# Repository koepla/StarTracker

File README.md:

# StarTracker

This repository is part of the diploma thesis of `Ilja Roman Köhler` and `Elias Engelbert Plank`. In short, the goal is to provide a software and hardware solution for the following question: Which technologies and algorithms are necessary to automatically track a range of different celestial bodies with an off the shelf camera?

---

## Contributors

[`Ilja Roman Köhler`](https://github.com/KoehIl180151 "Hardware part")

Responsible for the hardware, which involves designing and putting together a circuit that uses the almighty `ATMega-328p` chip as well as `TMC2209 drivers`, design and construction of the 3D-printed parts of the tracking mount, and firmware development for the circuit.

[`Elias Engelbert Plank`](https://github.com/PlanEl180223 "Software part")

Responsible for most of the software, which involves the ephemeris engine and the actual client application.

---

## How does StarTracker work?

To achieve the above goal, a construction made with the help of FDM printing, a circuit board, and a specially developed software are used. Specifically, an off the shelf camera mounted on the construction can be moved to any point in the sky by using stepper motors. By calculating the position of any celestial body in the client application, one can point the camera at basically anything that has spherical coordinates.

### Construction

The FDM parts were designed in a way so that they can be easily procued with any 3D printer (even entry-level devices) and still have the necessary stability. We recommend using PETG over PLA filament due to its superior material properties. The entire 3D design process is done in `Autodesk Fusion 360`, since Autodesk offers free licences for students, as well as a tool for designing circuit boards (`Autodesk Eagle`).

### Electronics and circuit

The camera is steered by `Nema 17 stepper motors`, which offer the perfect balance of power and size. The motors are driven by `TMC-2209 drivers` due to their reliability and robustness. The heart of the circuit is a `ATMega-328p` microcontroller, currently in the form of an Arduino Nano. However, there are plans to replace the Arduino Nano with just the ATMega chip itself.

### Client application

The client application, which is developed as a graphical desktop application entirely in C++ and GLSL, has a list of celestial bodies whose position can be computed. This list can be extended by the user. The position of each celestial body in the sky is determined in real time using our own ephemeris engine. When the user selects a target object, the position data is transmitted via a two-way protocol to the microcontroller on the circuit, whereupon the microcontroller sets the stepper motors to the correct position.

---

## Building

First of all, you must have git and CMake installed. As we use presets for our CMake configuration, you need a relatively recent version that supports presets. It is extremely important, that the repository is clonsed recursively, due to the use of submodules.

### Windows

On Windows, it is recommended to use Visual Studio 2022 together with the CMake extension. CMake will grab the dependencies upon configure, therefore no libraries have to be manually installed. You can then open the src/libtracker folder with Visual Studio that contains the CMakeLists.txt file. After CMake will finish with the configuration, you can choose a preset and build the application.

### Linux

On Linux, it is recommended to use JetBrains CLion, as it integrates with CMake. If you already have `curl` and `libcurl4-openssl-dev` installed, the CMake configuration will use those. Otherwise, curl will be automatically fetched, therefore no install is required. You can then open the src/libtracker folder with CLion. After CMake will finish with the configuration, you can choose a preset and build the application.

Here's a folder structure to feel secure and find your way around:

```
[root repo folder]
  |
  + [doc] // containing detailed project documentation
  |   |
  |   + [progress_reports] // containing status reports
  |                        // additionally github projects is used for documentation 
  |
  + [hwr] // containg schematics of the hardware parts
  |
  + [src] // containing the actual source code
      |
      + [tracker] // containing the code of the client application
      |   |
      |   + [libengine] // holds the source code of the ephemeris engine, builds to static library
      |   |
      |   + [libtracker] // the actual client application, links with libengine
      |
      + [firmware] // containing the firmware for the circuit
```

---

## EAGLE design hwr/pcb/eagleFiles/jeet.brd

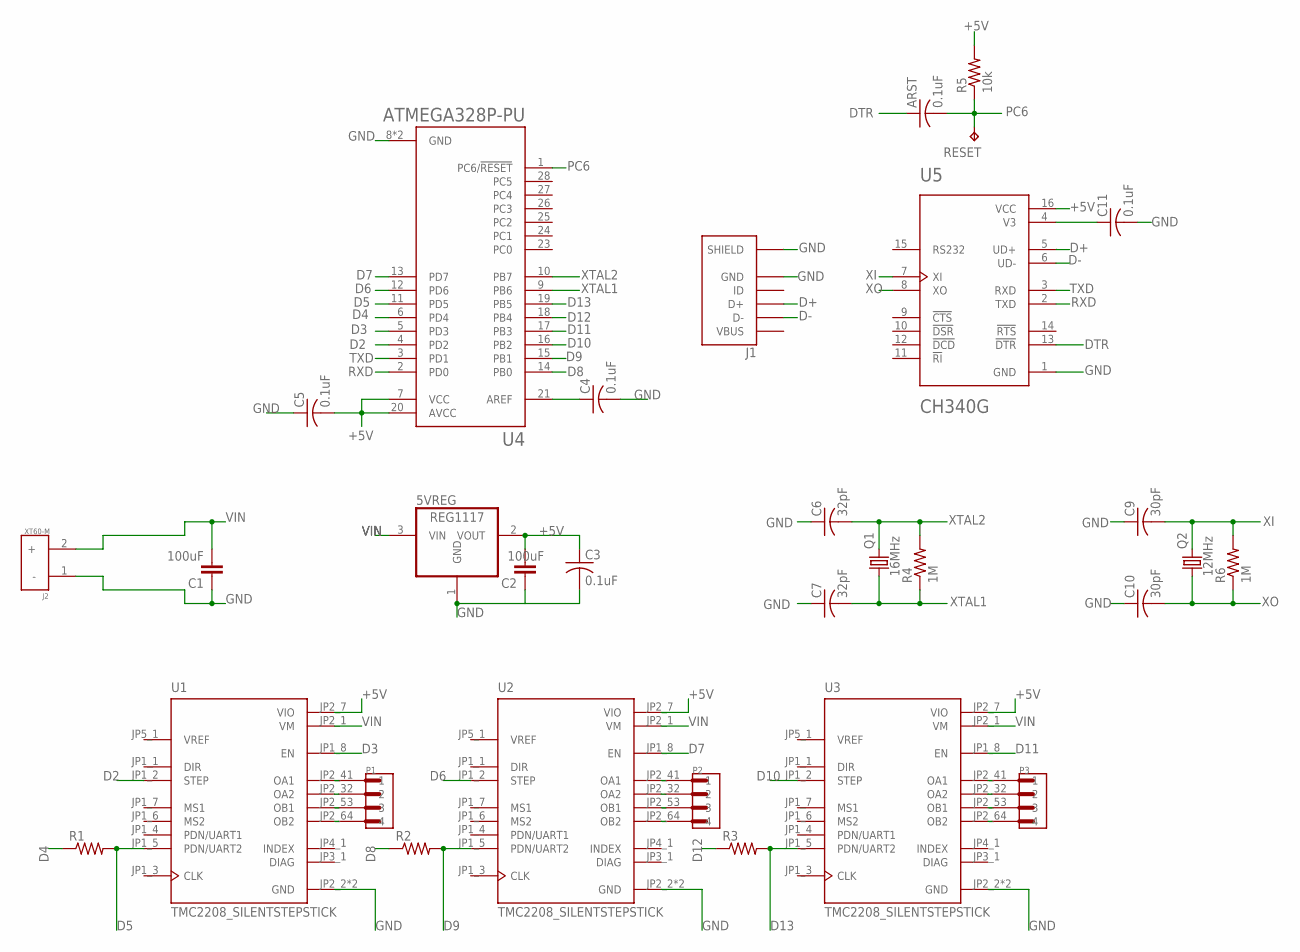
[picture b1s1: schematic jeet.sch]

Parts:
5VREG: REG1117; SOT223
ARST: 0.1uF; C0805
C1, C2: 100uF; C2.5-3
C3, C4, C5, C11: 0.1uF; C0805
C6, C7: 32pF; C0805
C9, C10: 30pF; C0805
J1: USB2066-05-RBHM-XX-STB-00-00-A_REVD; GCT_USB2066-05-RBHM-XX-STB-00-00-A_REVD
J2: XT60-M; AMASS_XT60-M
P1, P2, P3: S4B-XH-A(LF)(SN); JST_S4B-XH-A(LF)(SN)
Q1: 16MHz; HC49/S
Q2: 12MHz; HC49/S
R1, R2, R3: R-US_R0805; R0805
R4, R6: 1M; R0805
R5: 10k; R0805
RESET: TPB1,27; B1,27
U1, U2, U3: TMC2208_SILENTSTEPSTICK; MODULE_TMC2208_SILENTSTEPSTICK
U4: ATMEGA328P-PU; DIP794W46P254L2967H457Q28B
U5: CH340G; SOIC127P600X180-16N

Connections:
+5V: 5VREG.2 (VOUT), C2.2, C3.1, C5.2, R5.2, U1.JP2_7 (VIO), U2.JP2_7 (VIO), U3.JP2_7 (VIO), U4.7 (VCC), U4.20 (AVCC), U5.16 (VCC)
D2: U1.JP1_2 (STEP), U4.4 (PD2)
D3: U1.JP1_8 (EN), U4.5 (PD3)
D4: R1.1, U4.6 (PD4)
D5: R1.2, U1.JP1_5 (PDN/UART2), U4.11 (PD5)
D6: U2.JP1_2 (STEP), U4.12 (PD6)
D7: U2.JP1_8 (EN), U4.13 (PD7)
D8: R2.1, U4.14 (PB0)
D9: R2.2, U2.JP1_5 (PDN/UART2), U4.15 (PB1)
D10: U3.JP1_2 (STEP), U4.16 (PB2)
D11: U3.JP1_8 (EN), U4.17 (PB3)
D12: R3.1, U4.18 (PB4)
D13: R3.2, U3.JP1_5 (PDN/UART2), U4.19 (PB5)
D+: J1.3 (D+), U5.5 (UD+)
D-: J1.2 (D-), U5.6 (UD-)
DTR: ARST.1, U5.13 (!DTR)
GND: 5VREG.1 (GND), C1.1, C2.1, C3.2, C4.2, C5.1, C6.1, C7.1, C9.1, C10.1, C11.2, J1.5 (GND), J1.6 (SHIELD), J1.7 (SHIELD), J1.8 (SHIELD), J1.9 (SHIELD), J2.1 (-), U1.JP2_2 (GND), U1.JP2_8 (GND), U2.JP2_2 (GND), U2.JP2_8 (GND), U3.JP2_2 (GND), U3.JP2_8 (GND), U4.8 (GND), U4.22 (GND), U5.1 (GND)
unnamed: P1.1, U1.JP2_4 (OA1)
unnamed: P1.2, U1.JP2_3 (OA2)
unnamed: P1.3, U1.JP2_5 (OB1)
unnamed: P1.4, U1.JP2_6 (OB2)
unnamed: P2.1, U2.JP2_4 (OA1)
unnamed: P2.2, U2.JP2_3 (OA2)
unnamed: P2.3, U2.JP2_5 (OB1)
unnamed: P2.4, U2.JP2_6 (OB2)
unnamed: P3.1, U3.JP2_4 (OA1)
unnamed: P3.2, U3.JP2_3 (OA2)
unnamed: P3.3, U3.JP2_5 (OB1)
unnamed: P3.4, U3.JP2_6 (OB2)
unnamed: C4.1, U4.21 (AREF)
unnamed: C11.1, U5.4 (V3)
PC6: ARST.2, R5.1, RESET.TP, U4.1 (PC6/!RESET)
RXD: U4.2 (PD0), U5.2 (TXD)
TXD: U4.3 (PD1), U5.3 (RXD)
VBUS: J1.1 (VBUS)
VIN: 5VREG.3 (VIN), C1.2, J2.2 (+), U1.JP2_1 (VM), U2.JP2_1 (VM), U3.JP2_1 (VM)
XI: C9.2, Q2.2, R6.2, U5.7 (XI)
XO: C10.2, Q2.1, R6.1, U5.8 (XO)
XTAL1: C7.2, Q1.1, R4.1, U4.9 (PB6)
XTAL2: C6.2, Q1.2, R4.2, U4.10 (PB7)

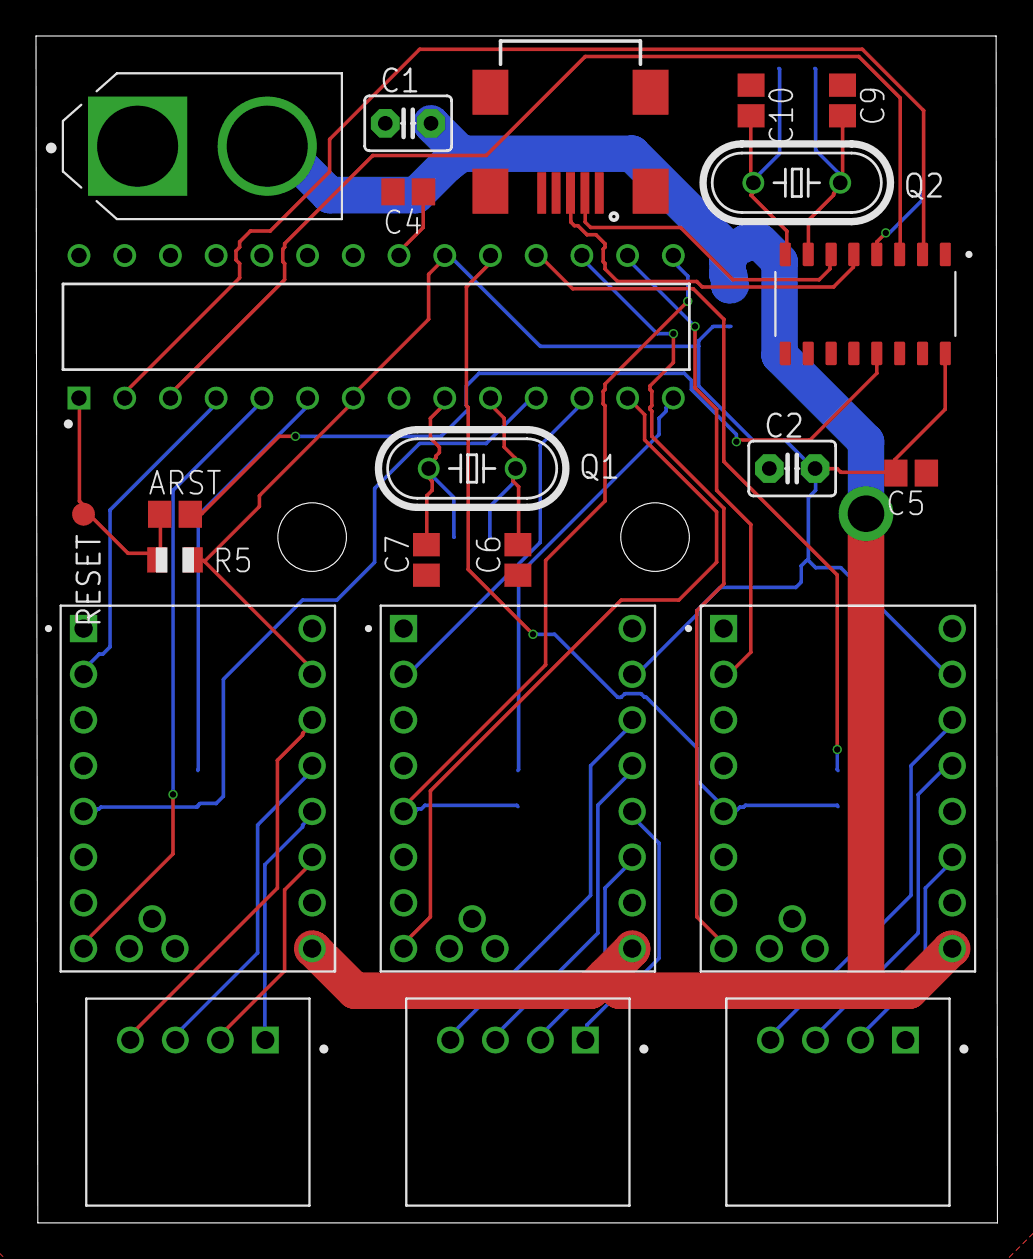
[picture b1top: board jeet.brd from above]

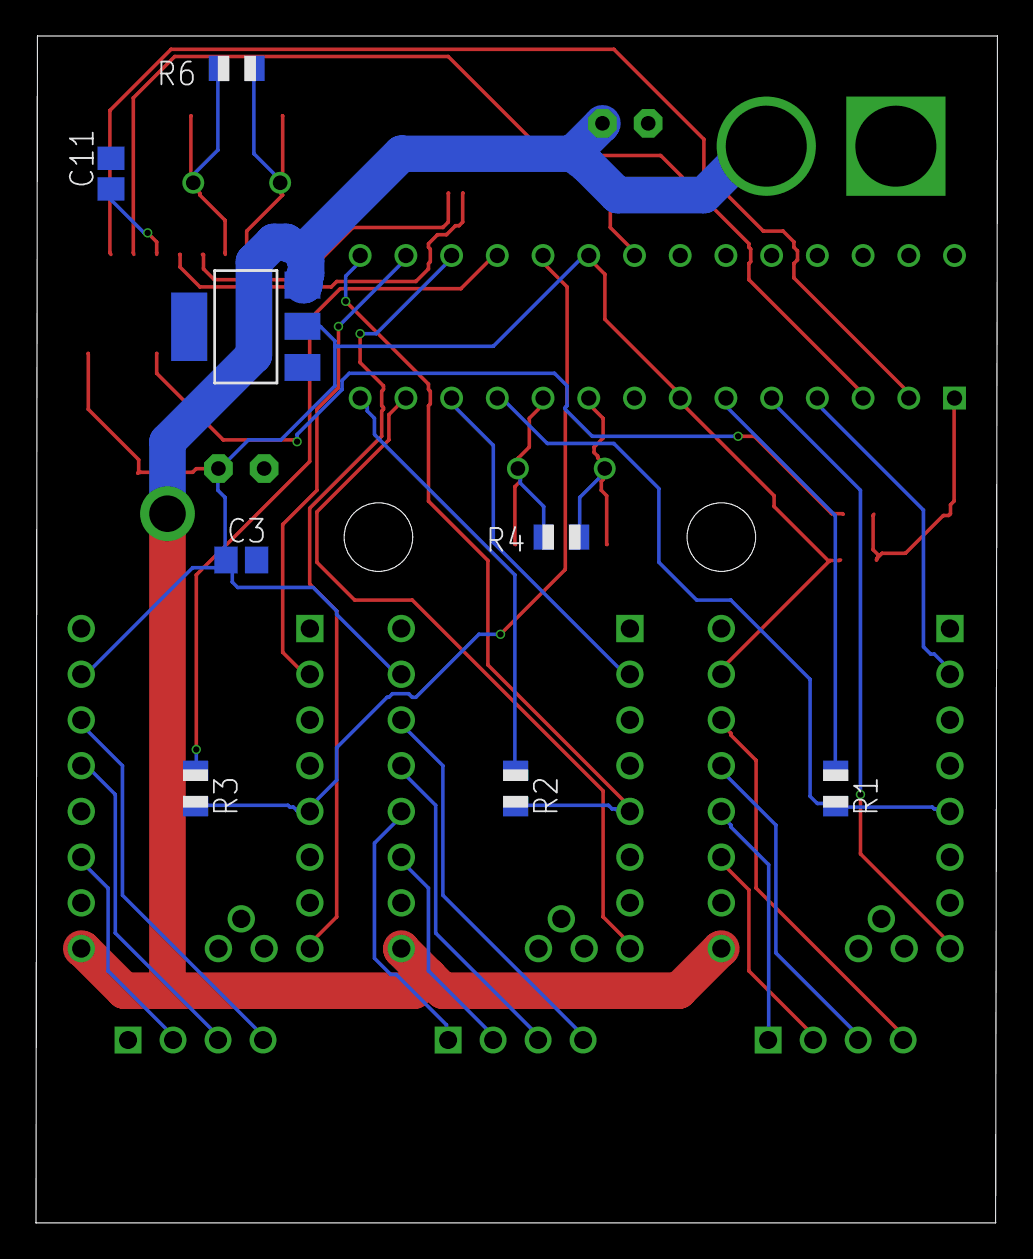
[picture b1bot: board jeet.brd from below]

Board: 4 copper layers, 53.4 x 65.9 mm, 31 parts (8 on the bottom side), 39 nets.

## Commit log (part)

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2021-11-04 accuracy
2021-11-04 code for testing
2021-11-04 can be const
2021-11-04 refactor
2021-11-04 more debug info
2021-11-04 temporary fix for coordinate transform
    the computed gmst was actually the local mean sidereal time, due to the fact that we passed the local time. If we want to still name the function Gmst, then we would only be allowed to pass the relat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
2021-11-04 added temporary compiler warning for potential unwanted behaviour in lmst function
2021-11-06 Added ability to adjust the tracker origin in softWare
2021-11-06 updated cli and added option for manual body
2021-11-13 added code for adding and subtracting parts of datetime
2021-11-13 fixed the issue with the computation of the local mean sidereal time
2021-11-13 testcases for the new datetime functions and sidereal time
2021-11-13 added serial to utils namespace
2021-11-14 removed testcases for datetime
2021-11-14 previous celestialbody is now solarsystem body
    added capability to add fixed bodies, previous celestialbody is now solarsystembody, LoadFromFile returns now a vector of unique pointers of celestialbodies due to polymorphism
2021-11-14 cosmetic
2021-11-14 update solarsystembody, celestialbody
2021-11-14 include
2021-11-14 added major galaxies and nebulas
2021-11-21 update work protocol
2021-12-03 better object oriented implementation
2021-12-03 missing core namespace
2021-12-03 added assert
2021-12-03 getline instead of cin
2021-12-04 unified member initialization
2021-12-04 set com-timeouts to one
2021-12-04 use const when possible
2021-12-04 use shared pointer because we may want to take ownership
2022-01-09 removed TMCStepper from include folder, should really use platform-io libraries
2022-01-09 option to use the waitcomm function or not
2022-01-09 minor refactoring
2022-01-09 minor refactor
2022-01-09 serial test
2022-01-13 update to visual studio 2022
2022-01-13 started work on application structure
2022-01-14 update work on application
2022-01-14 shouldn't be in here yet
2022-01-14 added sample app
2022-01-16 added fonts
2022-01-16 suppress external warning
2022-01-16 moved to another folder
2022-01-16 added optional vsync support
2022-01-16 added fonts in code
2022-01-16 update sample app
2022-01-16 update imgui ini
2022-01-16 added proper sample app
2022-01-16 view for sample app
2022-01-16 app class for sample app
2022-01-16 main method for sample app
2022-01-16 imgui ini for sample
2022-01-16 switch to std::string instead of const reference
2022-01-16 Added ExperimentalView for Mister Köhler to practice ImGui
2022-01-16 added ExperimentalView
2022-01-16 use vsync to reduce cpu usage
2022-01-16 this should get rid of apientry redefinition
2022-01-16 should be final
2022-01-17 add track button and calculate size
2022-01-18 fatal error, should be microseconds!
2022-01-26 changed the way we handle fonts
2022-01-28 added advanced tracking code
2022-01-30 Refactored the whole Driver Code
2022-01-30 Added possibility to set Tracking Duration
2022-01-30 minor changes
2022-01-30 this fixes the issue where we had to reupload the arduino code
2022-02-02 should not be inline
2022-02-02 nominmax
2022-02-05 Added functionality to check if the Tracker is still connected
2022-02-06 added input class
2022-02-12 rearanged files
2022-02-18 refactor ui, use utils::locationservice::location
2022-02-18 final because cool
2022-02-18 use shared_ptr of celestialbody, atomic bool to disallow parallel tracking
2022-02-18 warning
2022-02-19 structs should only carry data
2022-02-19 implemented basic event system
2022-02-19 fix underflow
2022-02-20 added bare minimum OpenGL requirements
2022-02-20 utility class for reading a file
2022-02-20 disable dockspace for opengl testing without framebuffer
2022-02-20 Add BufferLayout and BufferElement class
2022-02-20 Add VertexBuffer
2022-02-20 Add IndexBuffer
2022-02-20 Add Shader
2022-02-20 Add VertexArray
2022-02-20 shaders for testing
2022-02-20 debug environment using ExperimentalView
2022-02-22 remove test folder
2022-02-23 folder rename
2022-02-23 started Image class for image processing
2022-02-23 remove texture
2022-02-23 add imageprocessing
2022-02-23 add imageprocessing (hopefully the right folder now)
2022-02-23 remove image processing for now
2022-02-25 added texture support
2022-03-04 remove old startracker solution
2022-03-04 add clion cmake project
2022-03-04 added build command for copying assets
2022-03-04 added support for framebuffers
2022-03-05 debug callback, framebuffer fix
2022-03-05 fix framebuffer
2022-03-05 added StarTrackerView (root view)
2022-03-05 remove final
2022-03-06 added more mouseevents
2022-03-06 fixed framebuffer
2022-03-06 only resize on window resize
2022-03-11 implemented basic OpenGL Camera
2022-03-11 remove transform, update initial camera position
2022-03-12 debug callbacks should be set in window class
2022-03-12 add texturevertex
2022-03-12 shader should give more info, might change assert in the future
2022-03-12 added an assetdatabase
2022-03-12 added gpu image processing class
2022-03-14 attribute order
2022-03-14 added renderer, imageprocessingview
2022-03-14 added getters for width and height
2022-03-14 getters for ib and vb
2022-03-14 moved imageProcessingStuff to ImageProcessingView
2022-03-14 added ImageProcessingView
2022-03-14 save file and open file dialog
2022-03-14 ImageProcessing has to be initialized now,
    Maybe static method's don't make sense at this point
2022-03-14 added crashing version of stacking tab
2022-03-16 hardcode GL_RED format, this fixes crashing
2022-03-17 working but very hacky version
2022-03-17 more modern version of texture loading
2022-03-17 does work with every image now!
2022-03-17 title for ofd
2022-03-17 working ofd
2022-03-17 final fix
2022-03-18 First try to implement kernel (fail)
2022-03-18 working version of kernel ui
2022-03-18 shouldn't be here
2022-03-20 ui changes
2022-03-20 fix texture height
2022-03-20 don't care if only 2 texures are passed
2022-03-20 major ui refactor
2022-03-20 changed sharpening kernel
2022-03-20 accept only one texture
2022-03-24 added bom
2022-03-24 added gerber files
2022-03-24 added renders of pcb
2022-03-24 added eagle schematic file
2022-03-24 added eagle board file
2022-03-24 added eagle libaries
    added all libaries that where used in the eagle project for the PCB
2022-03-24 updated PCB schematic
2022-03-24 updated bom
2022-03-24 began to add links to used eagle libaries
2022-03-25 update ui
2022-03-27 add dark mode
2022-03-27 added setup script
2022-03-30 added custom allocator
2022-03-30 remove
2022-03-30 improve sanity checks
2022-04-01 first version of Model-Loading
2022-04-01 update dependency
2022-04-02 updated model and modelviewer
2022-04-02 update doc-strings in StarTracker::Core and StarTracker::Util
2022-04-02 antialiasing
2022-04-03 tabify all
2022-04-03 reformat
2022-04-03 tabify
2022-04-03 load normals and not color
2022-04-03 implement lighting for models
2022-04-03 added textureHandles to celestial bodies
2022-04-03 updated cad files
2022-04-03 updated .gitignore to include .obj
2022-04-03 added now allowed updated cad files
2022-04-04 some refactoring
2022-04-04 models
2022-04-04 added logging
2022-04-04 refactor
    should always forward
2022-04-04 remove exception from CelestialBody class, isn't really necessary here
2022-04-04 implement basic search engine for TrackableBodyView
    Note the comment
2022-04-04 this kinda needs a virtual destructor
2022-04-04 added renders of telescope holder
2022-04-04 update concept
2022-04-04 update demo image
2022-04-06 add celestial body library
2022-04-06 alter debug messages
2022-04-07 improve error handling
2022-04-07 updated 3d files
2022-04-07 updated renders of 3d models
2022-04-07 UI Code Refactor
2022-04-09 debug message refactor
2022-04-09 wrong pragma
2022-04-09 change to new ui api
2022-04-09 shared_ptr should not be passed as const reference, use std::string_view instead of const std::string& or std::string&&
2022-04-09 Made CelestialBodies Serializable
2022-04-09 Renamed CelestialBodyLibrary to BodyLibrary, made the BodyLibrary Serializable
2022-04-09 AssetDataBase holds complete BodyLibrary
2022-04-09 Function for Writing to a File
2022-04-10 std::string_view instead of const std::string&
2022-04-10 we want to store the path of the texture
2022-04-10 copy is necessary because GetDesignation and GetName are now returning string_view
2022-04-10 cursor stuff should really be in input
2022-04-10 added possibility to clear the logging vectors
2022-04-10 default dark mode
2022-04-10 colors changed, std::string_view
2022-04-10 optimizations
2022-04-10 pretty much reworking the image processing view, can currently load and stack textures, kernel stuff will be added soon, and we want to make use of the framebuffer layers
2022-04-10 different tracking menu (popup)
2022-04-11 bad default shader, isn't used anyway
2022-04-11 ui work (imageprocessing)
2022-04-12 user can now dynamically add entries to the body library
2022-04-12 supports solar system body now
2022-04-12 units
2022-04-12 improve cmakelists
2022-04-13 it is pretty stupid to use classes here, prefer free functions and organize them in a namespace
2022-04-13 fix aspect ratio on model
    we cannot assume that the size of the window is the size of the rendering viewport
2022-04-14 refactor, remove stupid auto for loop
2022-04-14 remove ambiguous definition for the runtime output directory
2022-04-14 optimize DateTime
2022-07-03 add dependency
2022-07-03 remove duplicate
2022-07-03 rename experimentalView to modelView
2022-07-03 change to fmt::format
2022-07-03 view for astronomical calculations
2022-07-03 minor refactor of main
2022-07-20 Last refactor before work continues at litec-thesis
2022-09-28 modified HD
    Modified HD housing so that it can be mounted to a nema 17 Stepper
2022-09-28 updated design
2023-03-13 Mirror: push changes from school repo
2023-08-19 NOISSUE fix wrong path in modules file
2025-04-16 chore(tracker): bump submodule dependencies
2025-04-16 chore(tracker): add cmake config for darwin
2025-04-16 chore(tracker): ensure compatibility with darwin
